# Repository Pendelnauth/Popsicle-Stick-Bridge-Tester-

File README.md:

# Popsicle Stick Bridge Tester
This is a basic Popsicle Stick Bridge Tester designed for use in a classroom environment.

# Back Story

This project was created to easily test popsicle stick bridges that students created as a part of the curriculum. This allows a safer and more accurate testing method compared to other more traditional methods.

# Project Notes

Because this is a one-off project little effort was put into refining the project. Certain aspects of the project need manual modification to allow for working functionality.
  1. The onboard regulator for the -5V rail only can produce -3.3V due to being fed 3.3v and a misunderstanding in the datasheet. The fix for this was to simply change the resistors to set the output voltage to -3V. Because the -5V rail is used to excite the load cell the output voltage is slightly lower making it more difficult to measure.
  2. ADC 16x gain input impedance. Due to the small voltage needed to be measured the internal PGA of the ADC is used to help achieve more stable readings from the load cells. This causes the input impedance of the ADC to drop off rapidly resulting in skewed measurements. To fix this additional oversampling (ADC-based) was applied as well as a rolling average(Program based) while using a lower gain. This kept the visually present noise down to an acceptable level. The preferred solution would be to either use a dedicated buffer or general-purpose amp before the ADC to drive it even at the lower input impedances adequately. Or make use of a purpose-built load cell measurement IC. 

Make sure to check out the User Manual for additional information and operation instructions.

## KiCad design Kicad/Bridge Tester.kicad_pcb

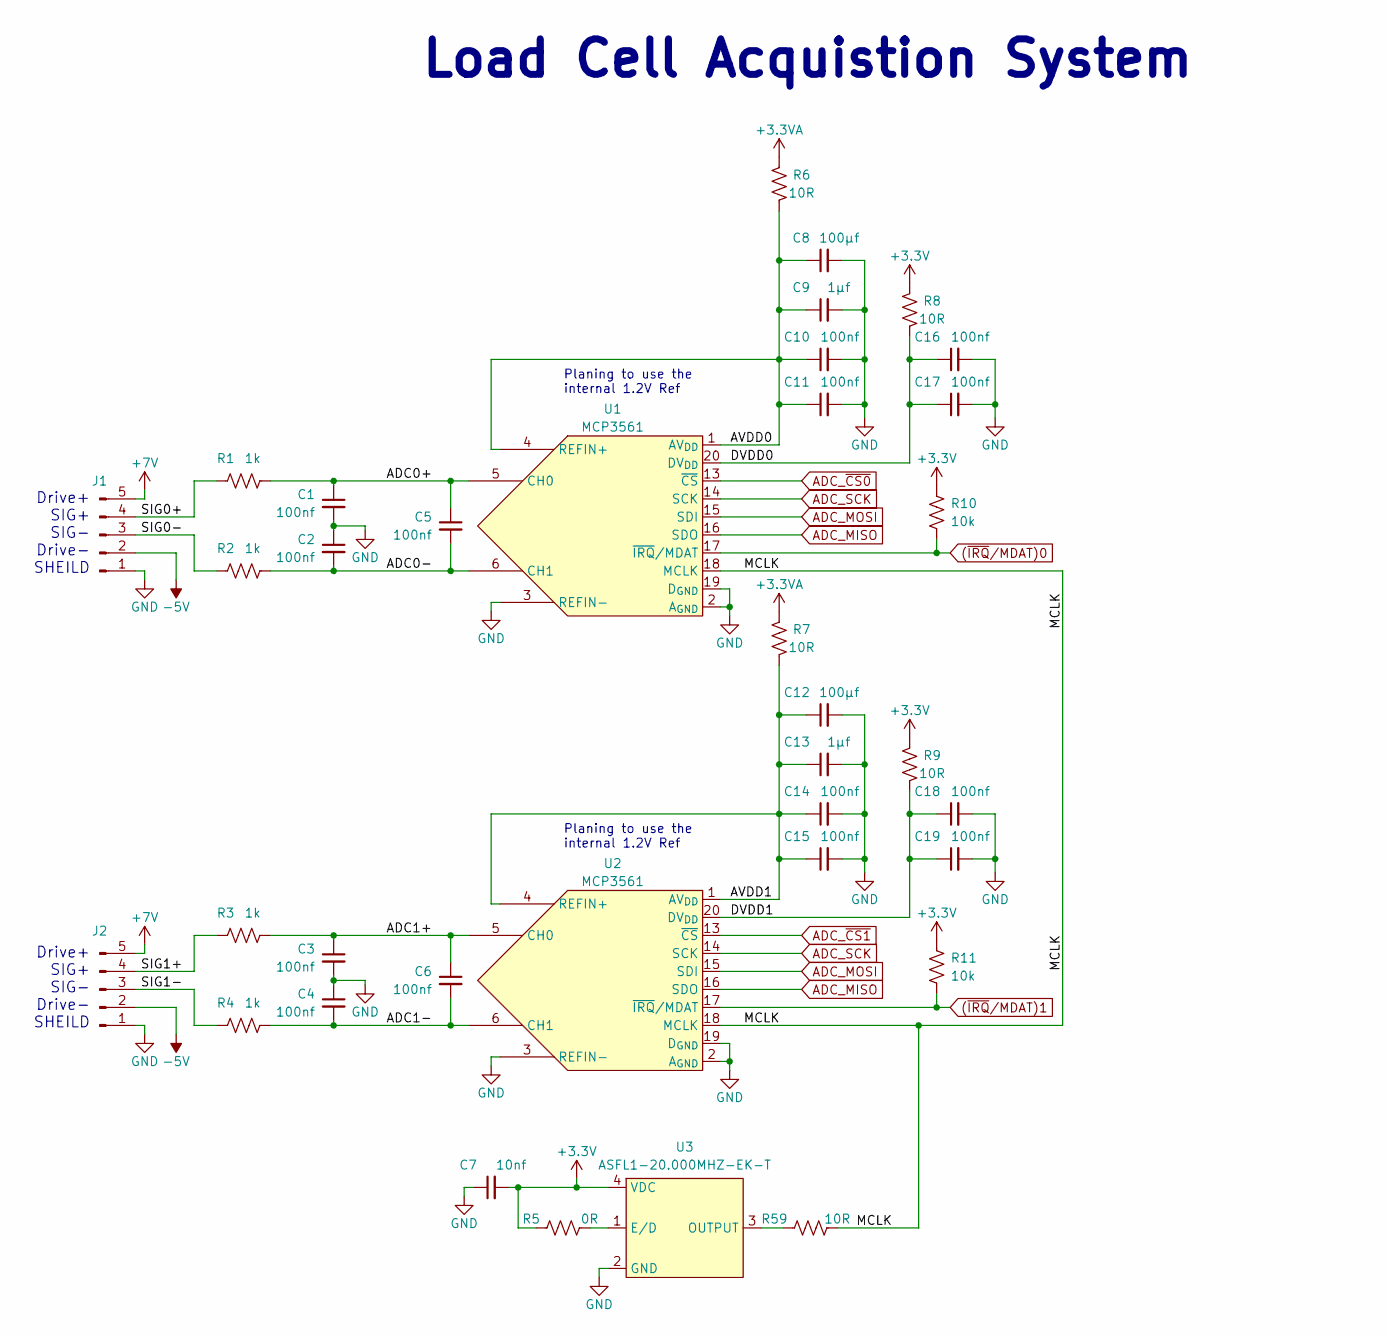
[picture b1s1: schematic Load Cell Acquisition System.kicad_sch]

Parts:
C1, C2, C3, C4, C5, C6, C10, C11, C14, C15, C16, C17, C18, C19: 100nf; C_0603_1608Metric
C7: 10nf; C_0603_1608Metric
C8, C12: 100μf; C_1206_3216Metric
C9, C13: 1μf; C_0603_1608Metric
J1, J2: Conn_01x05_Pin; JST_PH_B5B-PH-K_1x05_P2.00mm_Vertical
R1, R2, R3, R4: 1k; R_0603_1608Metric
R5: 0R; R_0603_1608Metric
R6, R7, R8, R9, R59: 10R; R_0603_1608Metric
R10, R11: 10k; R_0603_1608Metric
U1, U2: MCP3561; TSSOP-20_4.4x6.5mm_P0.65mm
U3: ASFL1-20.000MHZ-EK-T; 4-SMD

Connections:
(~IRQ/MDAT)0: R10.2, U1.17 (~IRQ/MDAT); also elsewhere on the board
(~IRQ/MDAT)1: R11.2, U2.17 (~IRQ/MDAT); also elsewhere on the board
+3.3V: C7.2, R5.1, R8.2, R9.2, R10.1, R11.1, U3.4 (VDC); also elsewhere on the board
+3.3VA: R6.2, R7.2; also elsewhere on the board
+7V: J1.5, J2.5; also elsewhere on the board
-5V: J1.2, J2.2; also elsewhere on the board
/Load Cell Acquisition System/ADC0+: C1.1, C5.1, R1.2, U1.5 (CH0)
/Load Cell Acquisition System/ADC0-: C2.2, C5.2, R2.2, U1.6 (CH1)
/Load Cell Acquisition System/ADC1+: C3.1, C6.1, R3.2, U2.5 (CH0)
/Load Cell Acquisition System/ADC1-: C4.2, C6.2, R4.2, U2.6 (CH1)
/Load Cell Acquisition System/AVDD0: C8.1, C9.1, C10.1, C11.1, R6.1, U1.1 (AV_{DD}), U1.4 (REFIN+)
/Load Cell Acquisition System/AVDD1: C12.1, C13.1, C14.1, C15.1, R7.1, U2.1 (AV_{DD}), U2.4 (REFIN+)
/Load Cell Acquisition System/DVDD0: C16.1, C17.1, R8.1, U1.20 (DV_{DD})
/Load Cell Acquisition System/DVDD1: C18.1, C19.1, R9.1, U2.20 (DV_{DD})
/Load Cell Acquisition System/MCLK: R59.2, U1.18 (MCLK), U2.18 (MCLK)
/Load Cell Acquisition System/SIG0+: J1.4, R1.1
/Load Cell Acquisition System/SIG0-: J1.3, R2.1
/Load Cell Acquisition System/SIG1+: J2.4, R3.1
/Load Cell Acquisition System/SIG1-: J2.3, R4.1
ADC_MISO: U1.16 (SDO), U2.16 (SDO); also elsewhere on the board
ADC_MOSI: U1.15 (SDI), U2.15 (SDI); also elsewhere on the board
ADC_SCK: U1.14 (SCK), U2.14 (SCK); also elsewhere on the board
ADC_~CS0: U1.13 (~CS); also elsewhere on the board
ADC_~CS1: U2.13 (~CS); also elsewhere on the board
GND: C1.2, C2.1, C3.2, C4.1, C7.1, C8.2, C9.2, C10.2, C11.2, C12.2, C13.2, C14.2, C15.2, C16.2, C17.2, C18.2, C19.2, J1.1, J2.1, U1.2 (A_{GND}), U1.3 (REFIN-), U1.19 (D_{GND}), U2.2 (A_{GND}), U2.3 (REFIN-), U2.19 (D_{GND}), U3.2 (GND); also elsewhere on the board
unnamed: R5.2, U3.1 (E/D)
unnamed: R59.1, U3.3 (OUTPUT)

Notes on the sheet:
Planing to use the internal 1.2V Ref
Drive+ SIG+ SIG- Drive- SHEILD
Load Cell Acquistion System

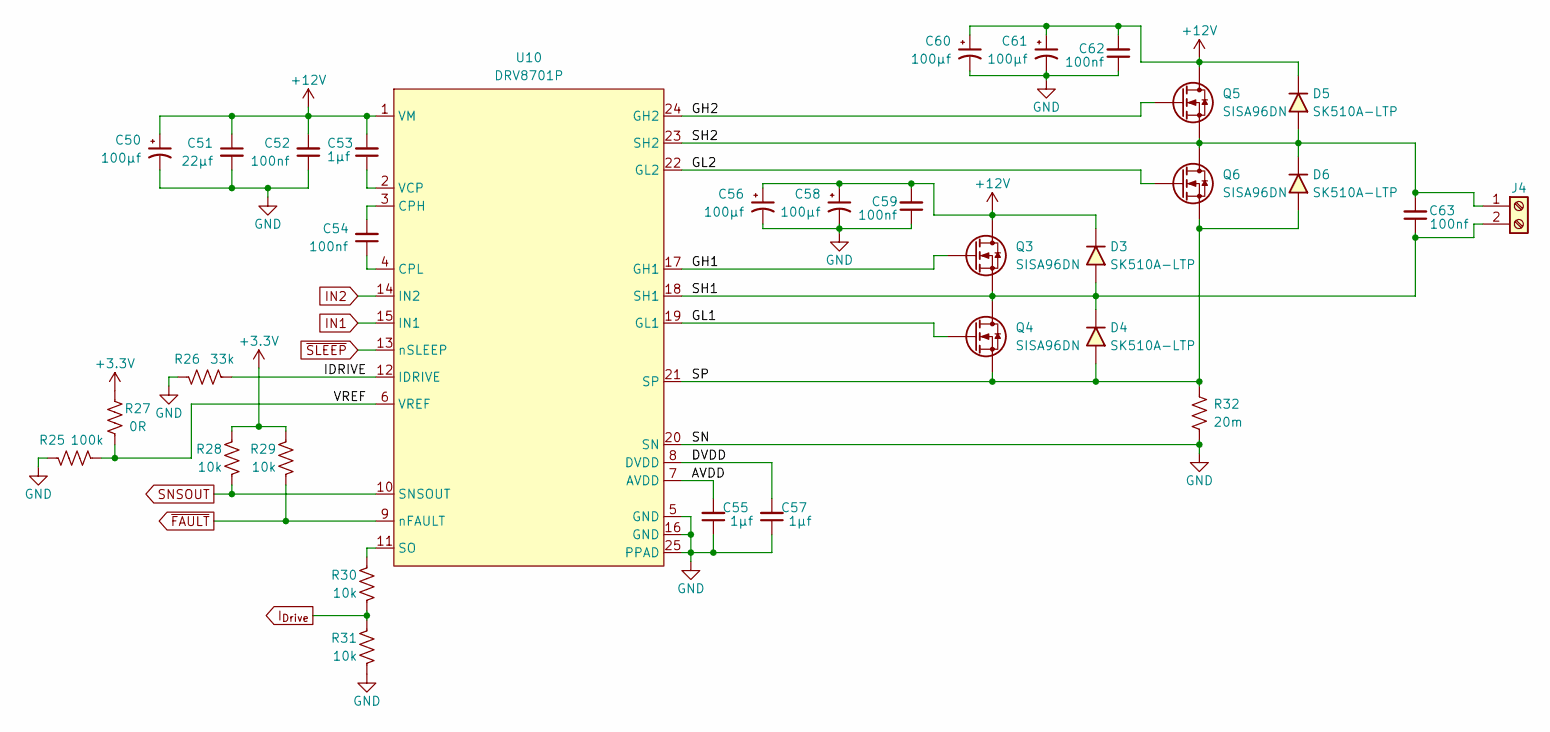
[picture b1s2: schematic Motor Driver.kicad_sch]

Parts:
C50, C56, C58, C60, C61: 100μf; CP_Elec_6.3x7.7
C51: 22μf; C_0805_2012Metric
C52, C54, C59, C62, C63: 100nf; C_0603_1608Metric
C53, C55, C57: 1μf; C_0603_1608Metric
D3, D4, D5, D6: SK510A-LTP; D_SMA
J4: Screw_Terminal_01x02; YK4410203000G
Q3, Q4, Q5, Q6: SISA96DN; Vishay_PowerPAK_1212-8_Single
R25: 100k; R_0603_1608Metric
R26: 33k; R_0603_1608Metric
R27: 0R; R_0603_1608Metric
R28, R29, R30, R31: 10k; R_0603_1608Metric
R32: 20m; R_2512_6332Metric
U10: DRV8701P; VQFN-24-1EP_4x4mm_P0.5mm_EP2.45x2.45mm_ThermalVias

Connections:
+3.3V: R27.1, R28.1, R29.1; also elsewhere on the board
+12V: C50.1, C51.1, C52.2, C53.2, C56.1, C58.1, C59.2, C60.1, C61.1, C62.2, D3.1 (K), D5.1 (K), Q3.5 (D), Q5.5 (D), U10.1 (VM); also elsewhere on the board
/Motor Driver/AVDD: C55.2, U10.7 (AVDD)
/Motor Driver/DVDD: C57.2, U10.8 (DVDD)
/Motor Driver/GH1: Q3.4 (G), U10.17 (GH1)
/Motor Driver/GH2: Q5.4 (G), U10.24 (GH2)
/Motor Driver/GL1: Q4.4 (G), U10.19 (GL1)
/Motor Driver/GL2: Q6.4 (G), U10.22 (GL2)
/Motor Driver/IDRIVE: R26.1, U10.12 (IDRIVE)
/Motor Driver/SH1: C63.1, D3.2 (A), D4.1 (K), J4.2, Q3.1 (S), Q3.2 (S), Q3.3 (S), Q4.5 (D), U10.18 (SH1)
/Motor Driver/SH2: C63.2, D5.2 (A), D6.1 (K), J4.1, Q5.1 (S), Q5.2 (S), Q5.3 (S), Q6.5 (D), U10.23 (SH2)
/Motor Driver/SP: D4.2 (A), D6.2 (A), Q4.1 (S), Q4.2 (S), Q4.3 (S), Q6.1 (S), Q6.2 (S), Q6.3 (S), R32.1, U10.21 (SP)
/Motor Driver/VREF: R25.1, R27.2, U10.6 (VREF)
GND: C50.2, C51.2, C52.1, C55.1, C56.2, C57.1, C58.2, C59.1, C60.2, C61.2, C62.1, R25.2, R26.2, R31.2, R32.2, U10.5 (GND), U10.16 (GND), U10.20 (SN), U10.25 (PPAD); also elsewhere on the board
IN1: U10.15 (IN1); also elsewhere on the board
IN2: U10.14 (IN2); also elsewhere on the board
I_{Drive}: R30.2, R31.1; also elsewhere on the board
unnamed: C54.2, U10.3 (CPH)
unnamed: C54.1, U10.4 (CPL)
unnamed: R30.1, U10.11 (SO)
unnamed: C53.1, U10.2 (VCP)
SNSOUT: R28.2, U10.10 (SNSOUT); also elsewhere on the board
~FAULT: R29.2, U10.9 (nFAULT); also elsewhere on the board
~SLEEP: U10.13 (nSLEEP); also elsewhere on the board

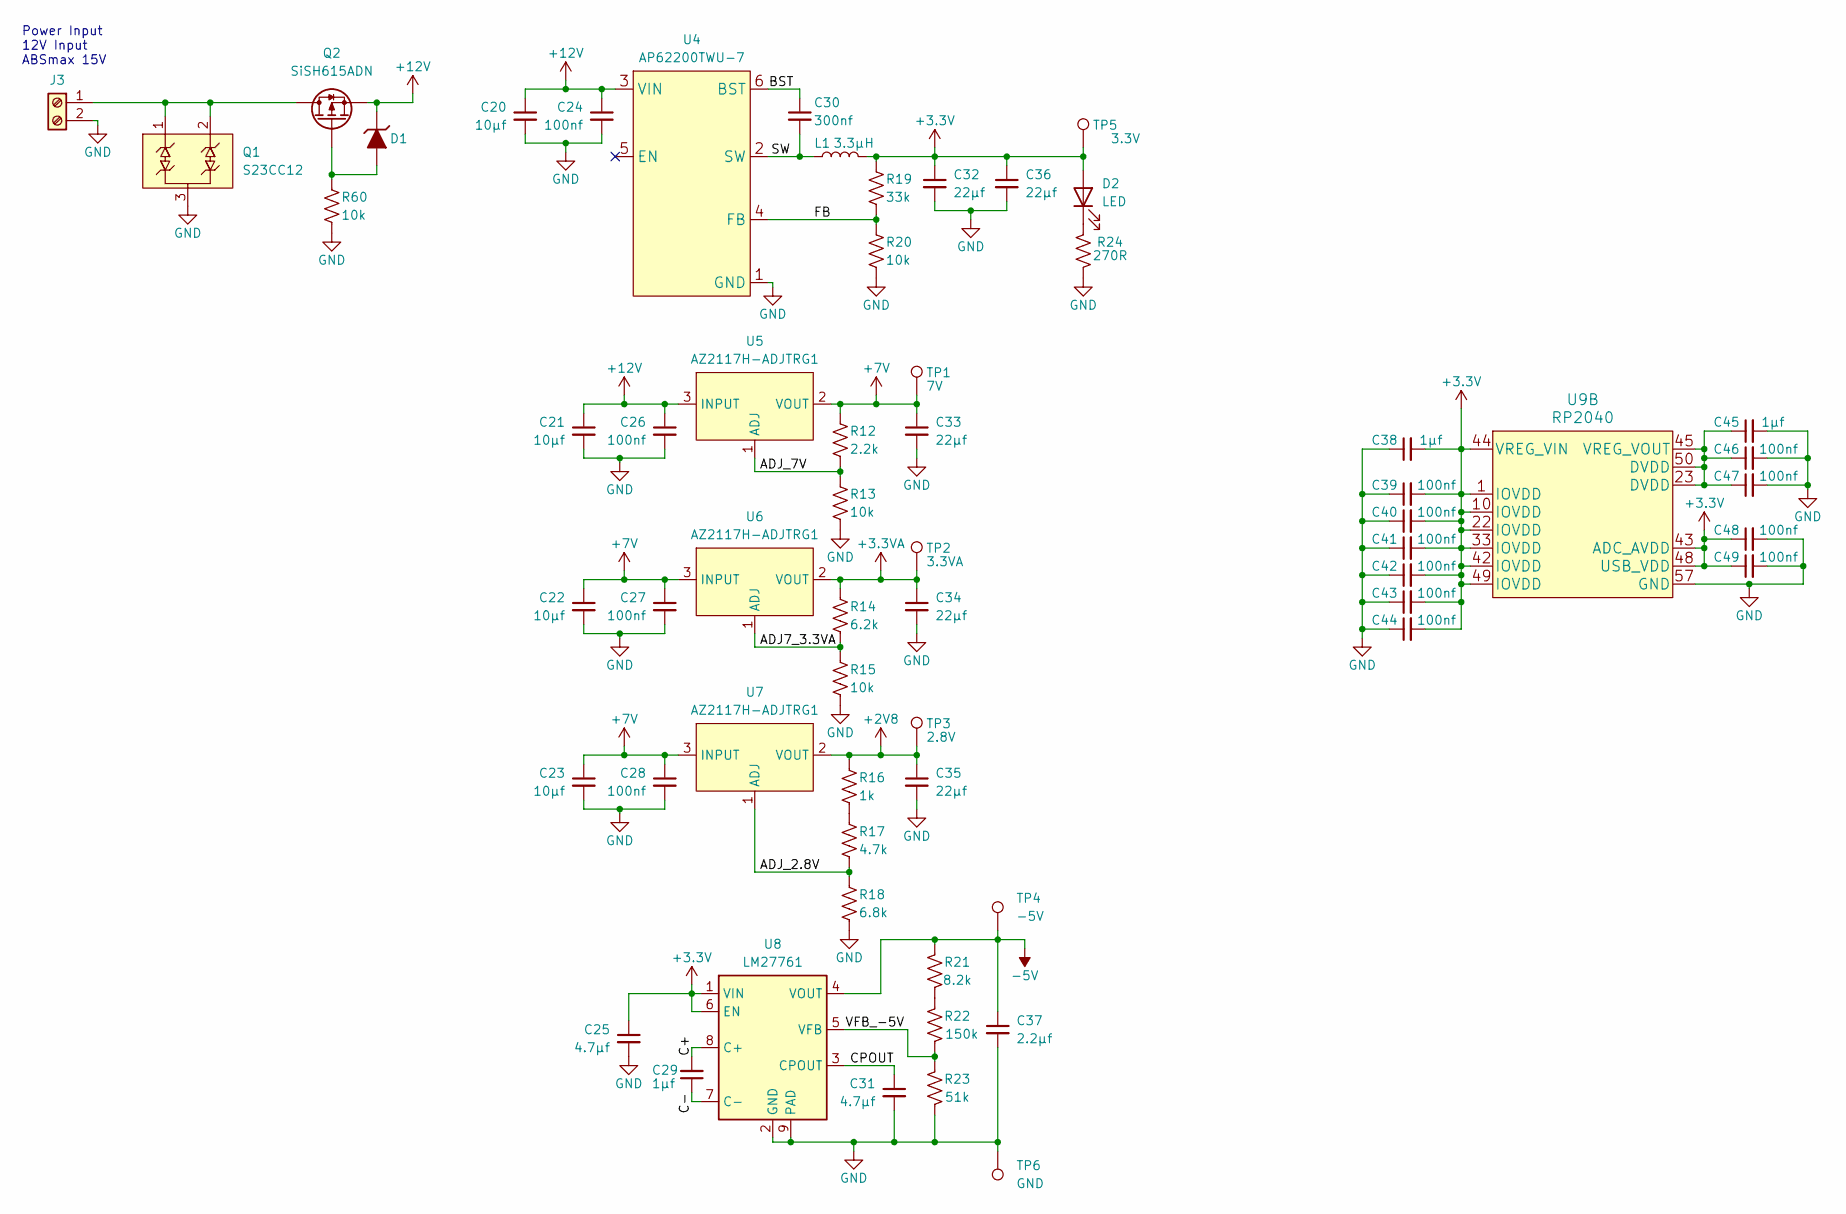
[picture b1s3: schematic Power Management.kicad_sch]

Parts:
C20, C21, C22, C23: 10μf; C_1206_3216Metric
C24, C26, C27, C28, C39, C40, C41, C42, C43, C44, C46, C47, C48, C49: 100nf; C_0603_1608Metric
C25, C31: 4.7μf; C_0805_2012Metric
C29, C38, C45: 1μf; C_0603_1608Metric
C30: 300nf; C_0603_1608Metric
C32, C33, C34, C35, C36: 22μf; C_0805_2012Metric
C37: 2.2μf; C_0805_2012Metric
D1: MMSZ5240B; D_SOD-123
D2: LED; LED_0603_1608Metric
J3: Screw_Terminal_01x02; YK4410203000G
L1: 3.3μH; APH0630T
Q1: S23CC12; SOT-23-3
Q2: SiSH615ADN; Vishay_PowerPAK_1212-8_Single
R12: 2.2k; R_0603_1608Metric
R13, R15, R20, R60: 10k; R_0603_1608Metric
R14: 6.2k; R_0603_1608Metric
R16: 1k; R_0603_1608Metric
R17: 4.7k; R_0603_1608Metric
R18: 6.8k; R_0603_1608Metric
R19: 33k; R_0603_1608Metric
R21: 8.2k; R_0603_1608Metric
R22: 150k; R_0603_1608Metric
R23: 51k; R_0603_1608Metric
R24: 270R; R_0603_1608Metric
TP1: 7V; TestPoint_Pad_D2.0mm
TP2: 3.3VA; TestPoint_Pad_D2.0mm
TP3: 2.8V; TestPoint_Pad_D2.0mm
TP4: -5V; TestPoint_Pad_D2.0mm
TP5: 3.3V; TestPoint_Pad_D2.0mm
TP6: GND; TestPoint_Pad_D2.0mm
U4: AP62200TWU-7; TSOT-23-6
U5, U6, U7: AZ2117H-ADJTRG1; SOT-223-3_TabPin2
U8: LM27761; WSON-8-1EP_2x2mm_P0.5mm_EP0.9x1.6mm
U9: RP2040

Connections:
+2V8: C35.1, R16.1, TP3.1, U7.2 (VOUT); also elsewhere on the board
+3.3V: C25.1, C32.1, C36.1, C38.2, C39.2, C40.2, C41.2, C42.2, C43.2, C44.2, C48.1, C49.1, D2.2 (A), L1.2, R19.1, TP5.1, U8.1 (VIN), U8.6 (EN), U9.1 (IOVDD), U9.10 (IOVDD), U9.22 (IOVDD), U9.33 (IOVDD), U9.42 (IOVDD), U9.43 (ADC_AVDD), U9.44 (VREG_VIN), U9.48 (USB_VDD), U9.49 (IOVDD); also elsewhere on the board
+3.3VA: C34.1, R14.1, TP2.1, U6.2 (VOUT); also elsewhere on the board
+7V: C22.1, C23.1, C27.1, C28.1, C33.1, R12.1, TP1.1, U5.2 (VOUT), U6.3 (INPUT), U7.3 (INPUT); also elsewhere on the board
+12V: C20.1, C21.1, C24.1, C26.1, D1.1 (K), Q2.1 (S), Q2.2 (S), Q2.3 (S), U4.3 (VIN), U5.3 (INPUT); also elsewhere on the board
-5V: C37.1, R21.2, TP4.1, U8.4 (VOUT); also elsewhere on the board
/Power Management/ADJ7_3.3VA: R14.2, R15.1, U6.1 (ADJ)
/Power Management/ADJ_2.8V: R17.2, R18.1, U7.1 (ADJ)
/Power Management/ADJ_7V: R12.2, R13.1, U5.1 (ADJ)
/Power Management/BST: C30.1, U4.6 (BST)
/Power Management/C+: C29.2, U8.8 (C+)
/Power Management/C-: C29.1, U8.7 (C-)
/Power Management/CPOUT: C31.1, U8.3 (CPOUT)
/Power Management/FB: R19.2, R20.1, U4.4 (FB)
/Power Management/SW: C30.2, L1.1, U4.2 (SW)
/Power Management/VFB_-5V: R22.1, R23.2, U8.5 (VFB)
GND: C20.2, C21.2, C22.2, C23.2, C24.2, C25.2, C26.2, C27.2, C28.2, C31.2, C32.2, C33.2, C34.2, C35.2, C36.2, C37.2, C38.1, C39.1, C40.1, C41.1, C42.1, C43.1, C44.1, C45.2, C46.2, C47.2, C48.2, C49.2, J3.2, Q1.3 (COM), R13.2, R15.2, R18.2, R20.2, R23.1, R24.2, R60.2, TP6.1, U4.1 (GND), U8.2 (GND), U8.9 (PAD), U9.57 (GND); also elsewhere on the board
unnamed: D1.2 (A), Q2.4 (G), R60.1
unnamed: D2.1 (K), R24.1
unnamed: J3.1, Q1.1 (C1), Q1.2 (C2), Q2.5 (D)
unnamed: R16.2, R17.1
unnamed: R21.1, R22.2
unnamed: C45.1, C46.1, C47.1, U9.23 (DVDD), U9.45 (VREG_VOUT), U9.50 (DVDD)

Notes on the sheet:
Power Input 12V Input ABSmax 15V

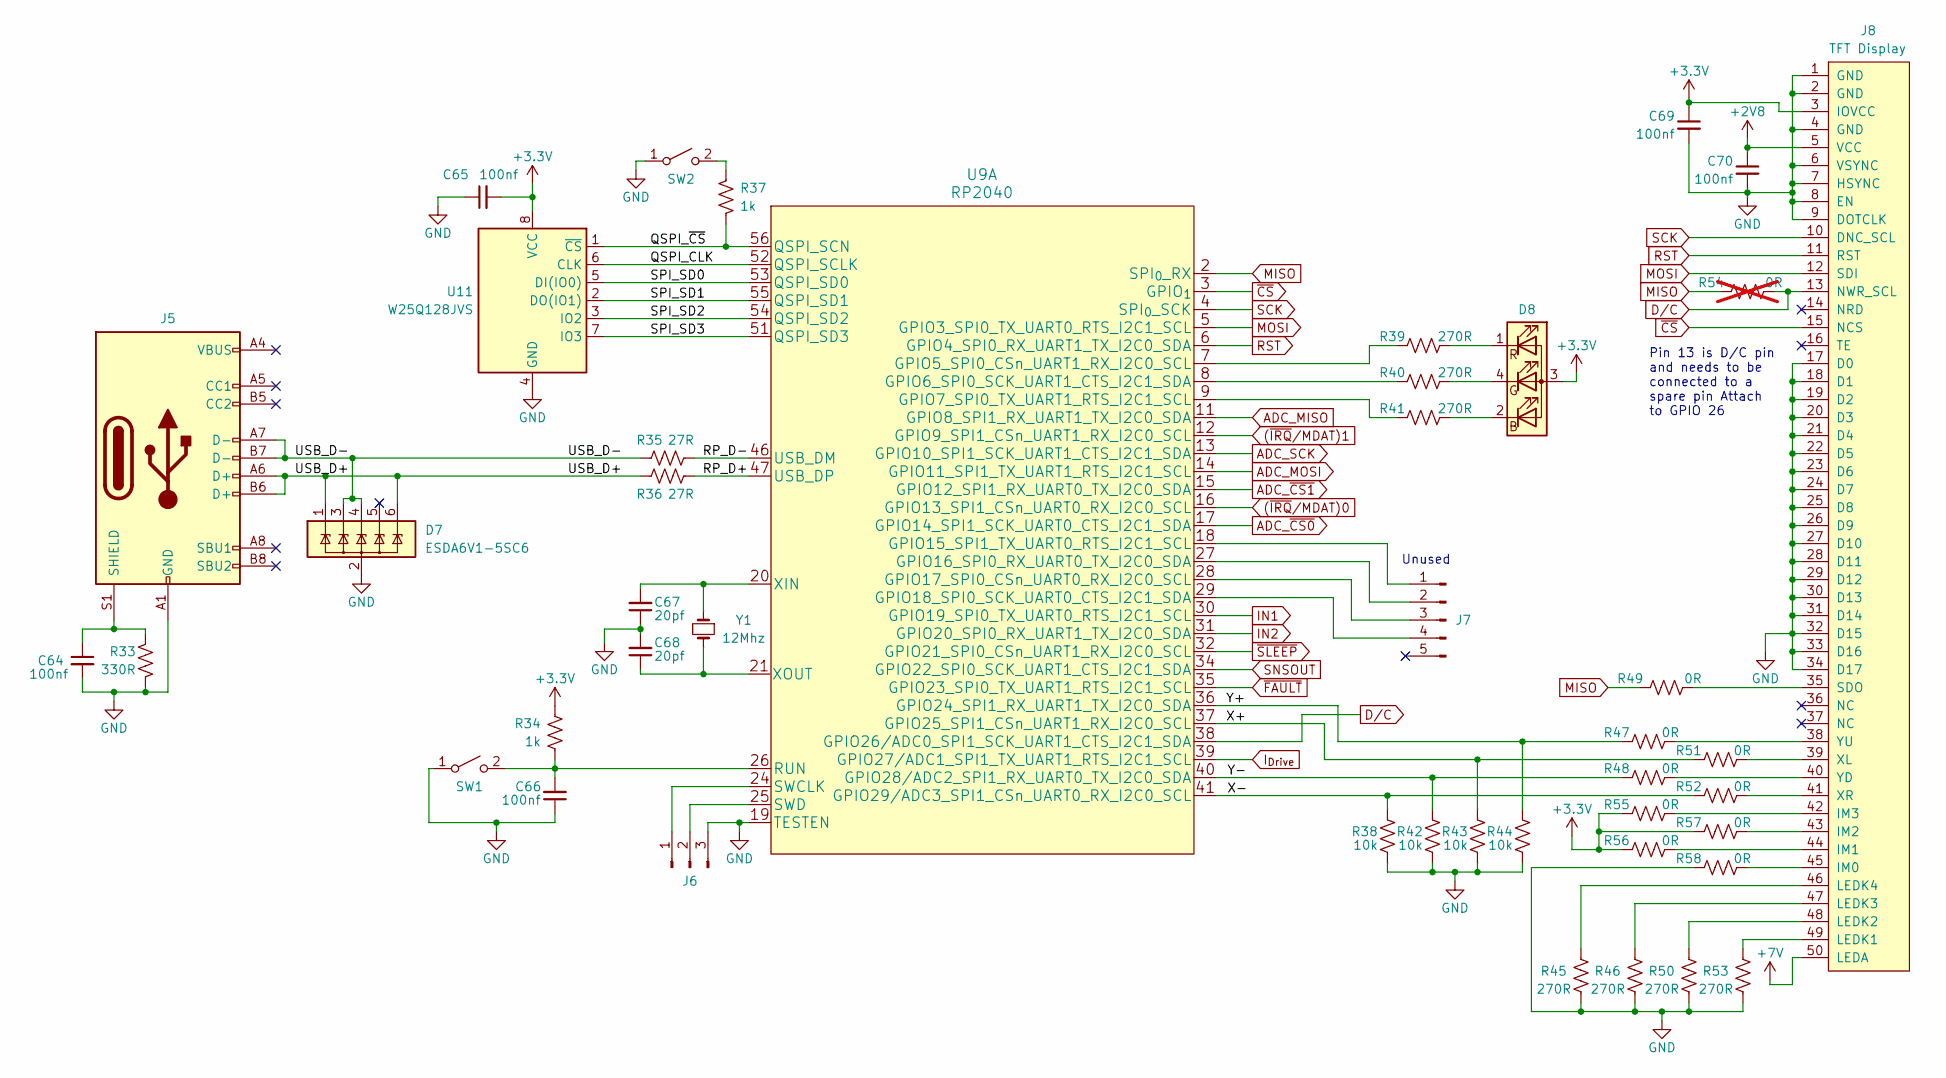
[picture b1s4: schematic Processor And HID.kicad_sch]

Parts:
C64, C65, C66, C69, C70: 100nf; C_0603_1608Metric
C67, C68: 20pf; C_0603_1608Metric
D7: ESDA6V1-5SC6; SOT-23-6
D8: LED_RBAG; 2.1x2.1 LED
J5: USB_C_Receptacle_USB2.0; USB_C_Receptacle_GCT_USB4105-xx-A_16P_TopMnt_Horizontal
J6: Conn_01x03_Pin; PinHeader_1x03_P2.54mm_Vertical
J7: Conn_01x05_Pin; PinHeader_1x05_P2.54mm_Vertical
J8: TFT Display; MOD-LCD2.8RTP
R33: 330R; R_0603_1608Metric
R34, R37: 1k; R_0603_1608Metric
R35, R36: 27R; R_0603_1608Metric
R38, R42, R43, R44: 10k; R_0603_1608Metric
R39, R40, R41, R45, R46, R50, R53: 270R; R_0603_1608Metric
R47, R48, R49, R51, R52, R55, R56, R57, R58: 0R; R_0603_1608Metric
R54: 0R; R_0603_1608Metric; not fitted
SW1, SW2: SW_SPST; SW_SPST_FSMSM
U9: RP2040
U11: W25Q128JVS; SOIC-8_5.23x5.23mm_P1.27mm
Y1: 12Mhz; Crystal_SMD_HC49-SD

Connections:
(~IRQ/MDAT)0: U9.16 (GPIO13_SPI1_CSn_UART0_RX_I2C0_SCL); also elsewhere on the board
(~IRQ/MDAT)1: U9.12 (GPIO9_SPI1_CSn_UART1_RX_I2C0_SCL); also elsewhere on the board
+2V8: C70.1, J8.5 (VCC); also elsewhere on the board
+3.3V: C65.2, C69.1, D8.3 (A), J8.3 (IOVCC), R34.2, R55.1, R56.1, R57.1, U11.8 (VCC); also elsewhere on the board
+7V: J8.50 (LEDA); also elsewhere on the board
/Processor And HID/QSPI_CLK: U9.52 (QSPI_SCLK), U11.6 (CLK)
/Processor And HID/QSPI_~CS: R37.1, U9.56 (QSPI_SCN), U11.1 (~CS)
/Processor And HID/RP_D+: R36.2, U9.47 (USB_DP)
/Processor And HID/RP_D-: R35.2, U9.46 (USB_DM)
/Processor And HID/SPI_SD0: U9.53 (QSPI_SD0), U11.5 (DI(IO0))
/Processor And HID/SPI_SD1: U9.55 (QSPI_SD1), U11.2 (DO(IO1))
/Processor And HID/SPI_SD2: U9.54 (QSPI_SD2), U11.3 (IO2)
/Processor And HID/SPI_SD3: U9.51 (QSPI_SD3), U11.7 (IO3)
/Processor And HID/USB_D+: D7.1 (IO1), D7.6 (IO5), J5.A6 (D+), J5.B6 (D+), R36.1
/Processor And HID/USB_D-: D7.3 (IO2), D7.4 (IO3), J5.A7 (D-), J5.B7 (D-), R35.1
/Processor And HID/X+: R43.2, R51.1, U9.37 (GPIO25_SPI1_CSn_UART1_RX_I2C0_SCL)
/Processor And HID/X-: R38.2, R52.1, U9.41 (GPIO29/ADC3_SPI1_CSn_UART0_RX_I2C0_SCL)
/Processor And HID/Y+: R44.2, R47.1, U9.36 (GPIO24_SPI1_RX_UART1_TX_I2C0_SDA)
/Processor And HID/Y-: R42.2, R48.1, U9.40 (GPIO28/ADC2_SPI1_RX_UART0_TX_I2C0_SDA)
ADC_MISO: U9.11 (GPIO8_SPI1_RX_UART1_TX_I2C0_SDA); also elsewhere on the board
ADC_MOSI: U9.14 (GPIO11_SPI1_TX_UART1_RTS_I2C1_SCL); also elsewhere on the board
ADC_SCK: U9.13 (GPIO10_SPI1_SCK_UART1_CTS_I2C1_SDA); also elsewhere on the board
ADC_~CS0: U9.17 (GPIO14_SPI1_SCK_UART0_CTS_I2C1_SDA); also elsewhere on the board
ADC_~CS1: U9.15 (GPIO12_SPI1_RX_UART0_TX_I2C0_SDA); also elsewhere on the board
D/C: J8.13 (NWR_SCL), R54.2, U9.38 (GPIO26/ADC0_SPI1_SCK_UART1_CTS_I2C1_SDA)
GND: C64.2, C65.1, C66.1, C67.1, C68.2, C69.2, C70.2, D7.2 (GND), J5.A1 (GND), J5.A12 (GND), J5.B1 (GND), J5.B12 (GND), J6.3, J8.1 (GND), J8.2 (GND), J8.4 (GND), J8.6 (VSYNC), J8.7 (HSYNC), J8.8 (EN), J8.9 (DOTCLK), J8.17 (D0), J8.18 (D1), J8.19 (D2), J8.20 (D3), J8.21 (D4), J8.22 (D5), J8.23 (D6), J8.24 (D7), J8.25 (D8), J8.26 (D9), J8.27 (D10), J8.28 (D11), J8.29 (D12), J8.30 (D13), J8.31 (D14), J8.32 (D15), J8.33 (D16), J8.34 (D17), R33.2, R38.1, R42.1, R43.1, R44.1, R45.1, R46.1, R50.1, R53.1, R58.1, SW1.1 (A), SW2.1 (A), U9.19 (TESTEN), U11.4 (GND); also elsewhere on the board
IN1: U9.30 (GPIO19_SPI0_TX_UART0_RTS_I2C1_SCL); also elsewhere on the board
IN2: U9.31 (GPIO20_SPI0_RX_UART1_TX_I2C0_SDA); also elsewhere on the board
I_{Drive}: U9.39 (GPIO27/ADC1_SPI1_TX_UART1_RTS_I2C1_SCL); also elsewhere on the board
MISO: R49.1, R54.1, U9.2 (SPI_{0}_RX)
MOSI: J8.12 (SDI), U9.5 (GPIO3_SPI0_TX_UART0_RTS_I2C1_SCL)
unnamed: D8.2 (BK), R41.1
unnamed: D8.4 (GK), R40.1
unnamed: D8.1 (RK), R39.1
unnamed: C64.1, J5.S1 (SHIELD), R33.1
unnamed: J6.1, U9.24 (SWCLK)
unnamed: J6.2, U9.25 (SWD)
unnamed: J7.1, U9.18 (GPIO15_SPI1_TX_UART0_RTS_I2C1_SCL)
unnamed: J7.2, U9.27 (GPIO16_SPI0_RX_UART0_TX_I2C0_SDA)
unnamed: J7.3, U9.28 (GPIO17_SPI0_CSn_UART0_RX_I2C0_SCL)
unnamed: J7.4, U9.29 (GPIO18_SPI0_SCK_UART0_CTS_I2C1_SDA)
unnamed: J8.45 (IM0), R58.2
unnamed: J8.44 (IM1), R56.2
unnamed: J8.43 (IM2), R57.2
unnamed: J8.42 (IM3), R55.2
unnamed: J8.49 (LEDK1), R53.2
unnamed: J8.48 (LEDK2), R50.2
unnamed: J8.47 (LEDK3), R46.2
unnamed: J8.46 (LEDK4), R45.2
unnamed: J8.35 (SDO), R49.2
unnamed: J8.39 (XL), R51.2
unnamed: J8.41 (XR), R52.2
unnamed: J8.40 (YD), R48.2
unnamed: J8.38 (YU), R47.2
unnamed: C66.2, R34.1, SW1.2 (B), U9.26 (RUN)
unnamed: R37.2, SW2.2 (B)
unnamed: R39.2, U9.7 (GPIO5_SPI0_CSn_UART1_RX_I2C0_SCL)
unnamed: R40.2, U9.8 (GPIO6_SPI0_SCK_UART1_CTS_I2C1_SDA)
unnamed: R41.2, U9.9 (GPIO7_SPI0_TX_UART1_RTS_I2C1_SCL)
unnamed: C67.2, U9.20 (XIN), Y1.1
unnamed: C68.1, U9.21 (XOUT), Y1.2
RST: J8.11 (RST), U9.6 (GPIO4_SPI0_RX_UART1_TX_I2C0_SDA)
SCK: J8.10 (DNC_SCL), U9.4 (SPI_{0}_SCK)
SNSOUT: U9.34 (GPIO22_SPI0_SCK_UART1_CTS_I2C1_SDA); also elsewhere on the board
~CS: J8.15 (NCS), U9.3 (GPIO_{1})
~FAULT: U9.35 (GPIO23_SPI0_TX_UART1_RTS_I2C1_SCL); also elsewhere on the board
~SLEEP: U9.32 (GPIO21_SPI0_CSn_UART1_RX_I2C0_SCL); also elsewhere on the board

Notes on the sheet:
Pin 13 is D/C pin and needs to be connected to a spare pin Attach to GPIO 26
Unused

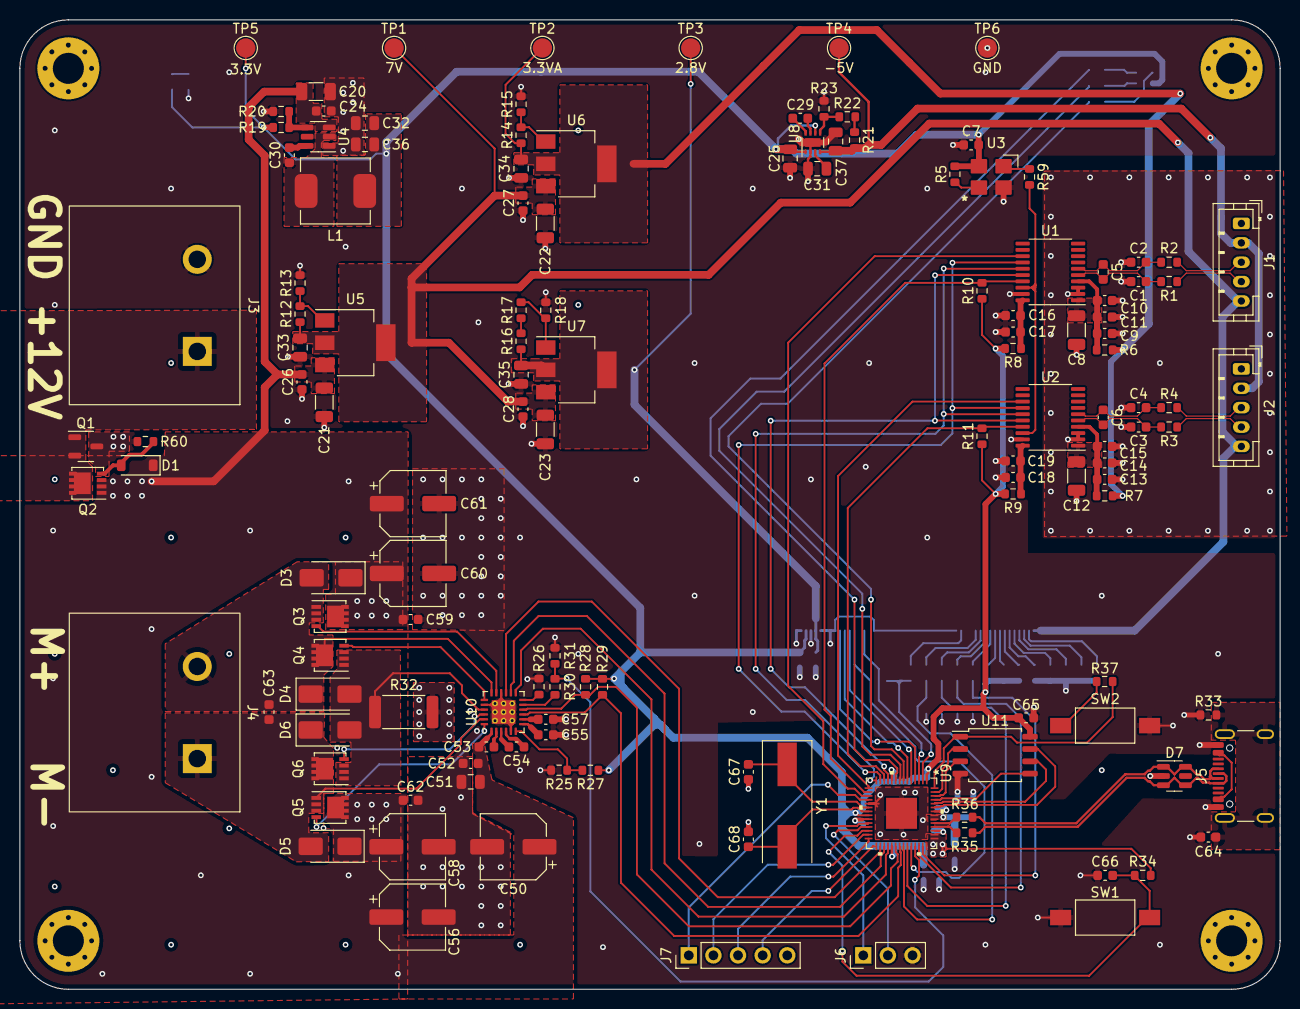
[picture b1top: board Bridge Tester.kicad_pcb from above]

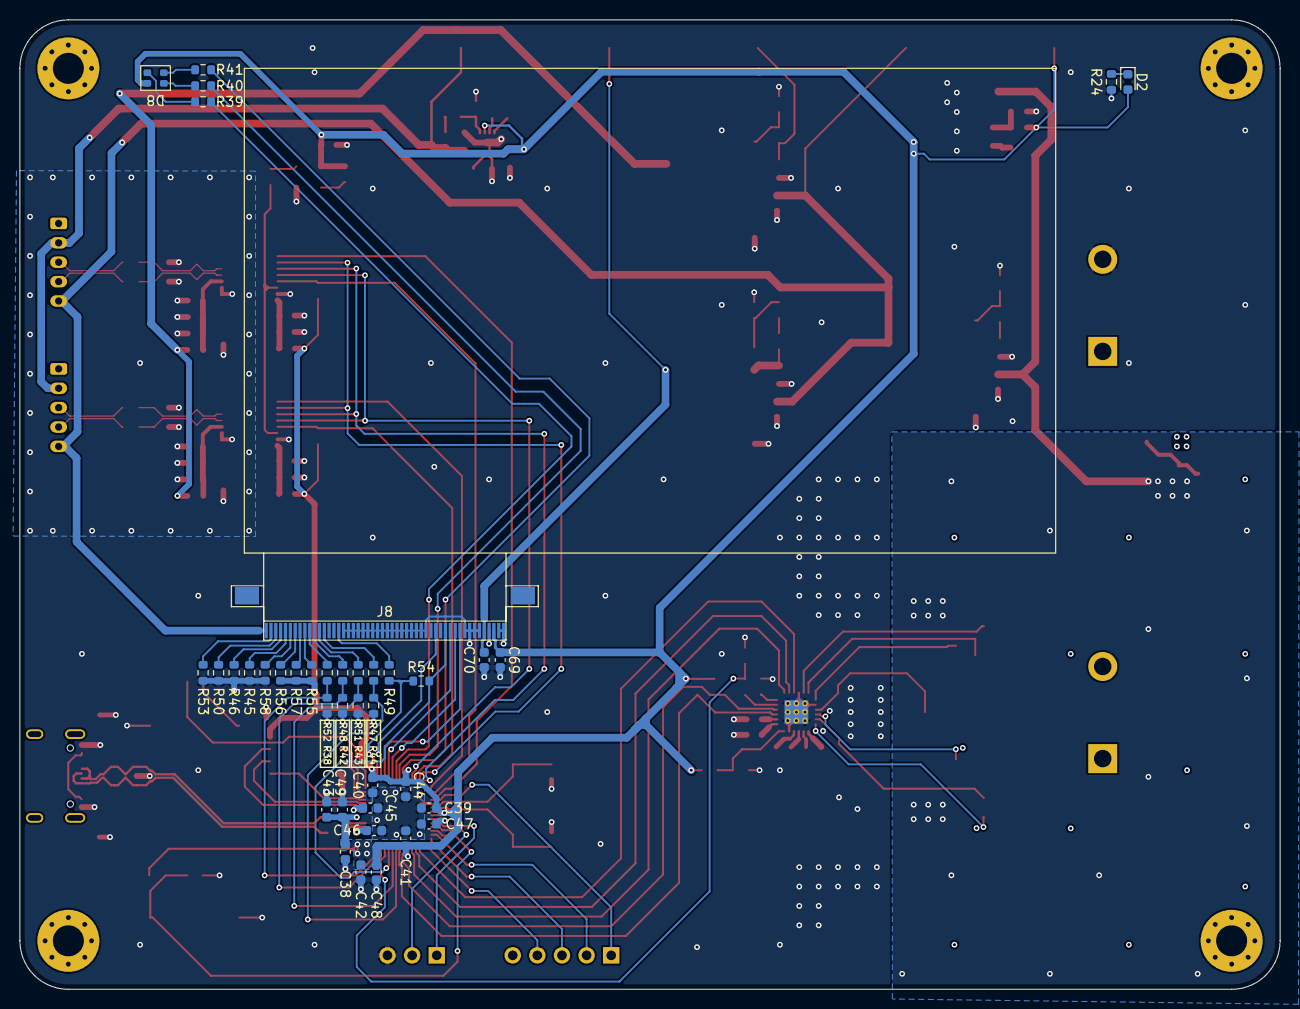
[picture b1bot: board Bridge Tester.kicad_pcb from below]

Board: 4 copper layers, 130.0 x 100.0 mm, 173 parts (39 on the bottom side), 116 nets.

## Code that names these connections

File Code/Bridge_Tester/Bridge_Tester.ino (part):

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#define IN2 20     //pwm2
#define NSleep 21  //motor controller sleep
#define NFault 23  //fault ouput from controller
#define SNSOut 22  //current chop active
#define IDrive 27  //Current Readout

//Display Pin Defs
#define Display_MISO 0  //display miso line
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#define LED_Blue 6

//ADC
#define ADC_MISO 8
#define ADC_MOSI 11
#define ADC_SCK 10
#define ADC_CS0 14
#define ADC_CS1 12
#define ADC_IRQ0 13
#define ADC_IRQ1 9

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  pinMode(IN2, OUTPUT_2MA);     //PWM1
  pinMode(NSleep, OUTPUT_2MA);  //place the Driver into Sleep mode when Low
  pinMode(NFault, INPUT);       //Fault Active low
  pinMode(SNSOut, INPUT);       //Current Chop Active
  pinMode(IDrive, INPUT);       //Current Readout from the Shunt amplifyer


  analogWriteFreq(50'000);
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
  SPI1.begin();

  pinMode(ADC_CS0, OUTPUT_12MA);  //cs0 is top adc
  pinMode(ADC_CS1, OUTPUT_12MA);
  pinMode(ADC_IRQ0, INPUT);
  pinMode(ADC_IRQ1, INPUT);

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
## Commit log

2024-12-23 Update README.md
    Added Project notes and back story to the readme.
2024-12-23 Update README.md
    Formating fix?
2024-12-23 Update README.md
    formating fix
2024-12-23 Create KiCad.gitignore
    Added kicad gitignore
2024-12-23 Create Other.gitignore
    Create and add other gitignore arguments to remove some other unnecessary files.
2024-12-23 Add files via upload
    Code Upload
2024-12-23 Add files via upload
    Docs Upload
2024-12-23 Add files via upload
    CAD upload
2024-12-23 Add files via upload
    Kicad Upload
